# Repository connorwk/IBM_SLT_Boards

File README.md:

# IBM_SLT_Boards
IBM SLT board schematics/reproductions

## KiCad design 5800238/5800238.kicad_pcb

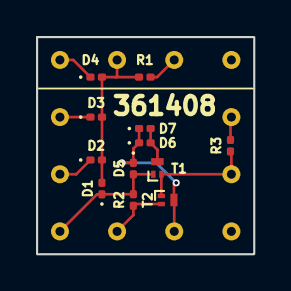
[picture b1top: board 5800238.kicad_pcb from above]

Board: 2 copper layers, 12.1 x 12.1 mm, 13 parts (0 on the bottom side), 11 nets.

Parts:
D1, D2, D3, D4, D5, D6, D7: IBM_Diode; D_0201_0603Metric
R1: 1.2K; R_0201_0603Metric
R2: 1.8K; R_0201_0603Metric
R3: 1K; R_0201_0603Metric
T1: T_DB; Diodes_DFN1006-3
T2: T_DA; Diodes_DFN1006-3
U1: 12-Pin_SLx_Can

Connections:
/1: D1.1 (K), D5.2 (A), R2.1, T1.1 (B), U1.1
/2: D2.1 (K), U1.2
/3: D3.1 (K), U1.3
/4: D4.1 (K), U1.4
/5: D1.2 (A), D2.2 (A), D3.2 (A), D4.2 (A), R1.2, U1.5
/7: D6.2 (A), D7.2 (A), T1.3 (C), U1.7
/9: R3.1, T1.2 (E), T2.1 (B), U1.9
/11: D5.1 (K), D6.1 (K), D7.1 (K), T2.3 (C), U1.11
/+6V: R1.1, U1.6
/-3V: R3.2, U1.8
GND: R2.2, T2.2 (E), U1.12

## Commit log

2023-01-18 gitignore
2023-01-18 Initial schematic for 5804664
2023-01-18 update gitignore
2023-01-18 add pdf
2023-01-18 Changed input for invert to keep from pulling to 0V
2023-01-30 File name change for schematic, and initial files for 5803024 and 5804615
2023-02-04 Base schematic with cans created for 5804672 and 5806213
2023-02-04 Base schematic with cans created for 5803757
2023-02-05 Base schematic with cans created for 5804610
2023-02-05 Base schematic with cans created for 5804625
2023-02-05 Base schematic with cans created for 5804624
2023-02-05 Base schematic with cans created for 5804621
2023-02-05 Remove extranious labels
2023-02-05 Base schematic with cans created for 5803481
2023-02-05 Schematic for 5800238
2023-02-05 Schematic for 5800509
2023-02-05 Schematic for 5800000
2023-02-05 Base schematic with cans created for 5803815
2023-02-05 Base schematic with cans created for 5803761
2023-02-05 Base schematic with cans created for 5803022
2023-02-05 Base schematic with cans created for 5803016
2023-02-05 Remove extra labels
2023-02-05 Base schematic with cans created for 5803817
2023-02-05 Base schematic with cans created for 5804680
2023-02-06 Base schematic with cans created for 5806207
2023-02-06 Base schematic with cans created for 5804607
2023-02-06 Base schematic with cans created for 5804616
2023-02-06 Base schematic with cans created for 5806251
2023-02-06 Base schematic with cans created for 5806257
2023-02-06 Base schematic with cans created for 5807317
2023-02-06 Base schematic with cans created for 5803794
2023-02-06 Base schematic with cans created for 5804685
2023-02-06 Base schematic with cans created for 5807312
2023-02-06 Base schematic with cans created for 5804614
2023-02-06 Base schematic with cans created for 5803447
2023-02-06 Base schematic with cans created for 5806220
2023-02-06 Base schematic with cans created for 5803819
2023-02-06 Base schematic with cans created for 5803816
2023-02-06 Base schematic with cans created for 5803793
2023-02-06 Base schematic with cans created for 5806217
2023-02-06 Test project for Spice simulation
2023-02-12 Start of 1130 backplane. IO Bus connections made using ALD pages BB101-BB141
2023-02-12 Removed power rails off 01A-C1 N2 connector
2023-02-12 DN101-DN111 added to backplane schematics, DN111 01B-A1 connections made, 01B-B1 connections to be made when all signals on connectors
2023-02-13 Add labels for cable runs, completed tracing for DN111 from previous commit, decided it would be too much work to go back and route later... Completed DN201 page.
2023-02-13 Add labels for bottom T[x] connectors, finished page DU101.
2023-02-13 Fix routing mistake from DU101 for T6, was 01A-A1 to 01A-B1, corrected from 01A-A1 to 01A-C1, finished page DU111.
2023-02-13 Finish page KA101-KA111
2023-02-13 Finish page KB101-KB111
2023-02-13 Finish page KC101-KC111
2023-02-13 Finish page KD101-KD111
2023-02-13 Redo annotations...
2023-02-13 Finish page KG101-KG151
2023-02-13 Finish page KG201-KG111
2023-02-13 Finish page KG221-KG151
2023-02-13 Finish page KM101-KM111
2023-02-13 Finish page KM201-KM211
2023-02-13 Finish page KM301-KM321
2023-02-13 Finish page KR101-KR111
2023-02-14 Finish page KS101-KS111
2023-02-14 Finish page KT101-KT131
2023-02-14 Finish page KT201
2023-02-14 Finish page KT301-KT331
2023-02-14 Finish page KU101-KU111
2023-02-14 Finish page KU201-KU211
2023-02-14 Finish page KU301-KU311, minor column label fix.
2023-02-14 Finish page KW101. Add 48V bus for 01A-C1
2023-02-14 Finish page MB101
2023-02-15 Actually finish MB101...
2023-02-15 Finish page MB201
2023-02-15 Finish page MC101
2023-02-15 Finish page RA101-RA171
2023-02-15 Finish page RA201-RA271
2023-02-15 Finish page RB101-RB171 and RB201-RB271
2023-02-15 Finish page RB301-RB321
2023-02-15 Finish page RD101-RD171
2023-02-15 Finish page RN101-RN111
2023-02-15 Finish page RN101-RN111, forgot DOT OR
2023-02-15 Finish page RQ101-RQ171
2023-02-15 Finish page RS101-RS121, Processor logic finished! Now for I/O and Memory.
2023-02-15 Finish page WZ051 and WZ061
2023-02-19 Schematic for 5803765 done! Based on 5803493, one cap needs to be measured out of circuit to complete.
